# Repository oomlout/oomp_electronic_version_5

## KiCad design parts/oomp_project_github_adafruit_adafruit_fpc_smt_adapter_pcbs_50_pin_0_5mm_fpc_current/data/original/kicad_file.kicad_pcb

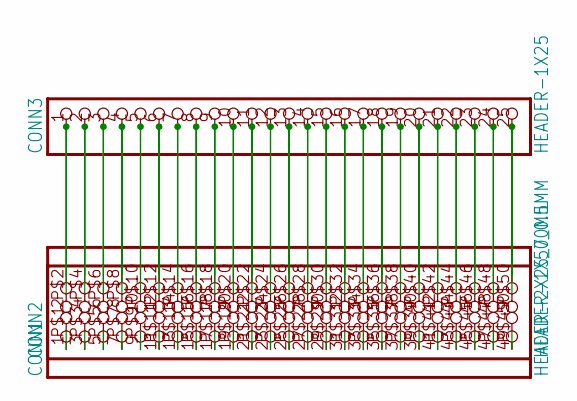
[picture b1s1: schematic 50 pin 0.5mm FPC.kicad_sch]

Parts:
CONN1: HEADER-2X25_70MIL; 2X25
CONN2: HEADER-1X50_0.5MM; FPC_GENERIC_0.5MM_50PIN
CONN3: HEADER-1X25; 1X25_ROUND_70MIL

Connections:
unnamed: CONN1.1, CONN2.P$1 (1)
unnamed: CONN1.2, CONN2.P$2 (2), CONN3.1
unnamed: CONN1.3, CONN2.P$3 (3)
unnamed: CONN1.4, CONN2.P$4 (4), CONN3.2
unnamed: CONN1.5, CONN2.P$5 (5)
unnamed: CONN1.6, CONN2.P$6 (6), CONN3.3
unnamed: CONN1.7, CONN2.P$7 (7)
unnamed: CONN1.8, CONN2.P$8 (8), CONN3.4
unnamed: CONN1.9, CONN2.P$9 (9)
unnamed: CONN1.10, CONN2.P$10 (10), CONN3.5
unnamed: CONN1.11, CONN2.P$11 (11)
unnamed: CONN1.12, CONN2.P$12 (12), CONN3.6
unnamed: CONN1.13, CONN2.P$13 (13)
unnamed: CONN1.14, CONN2.P$14 (14), CONN3.7
unnamed: CONN1.15, CONN2.P$15 (15)
unnamed: CONN1.16, CONN2.P$16 (16), CONN3.8
unnamed: CONN1.17, CONN2.P$17 (17)
unnamed: CONN1.18, CONN2.P$18 (18), CONN3.9
unnamed: CONN1.19, CONN2.P$19 (19)
unnamed: CONN1.20, CONN2.P$20 (20), CONN3.10
unnamed: CONN1.21, CONN2.P$21 (21)
unnamed: CONN1.22, CONN2.P$22 (22), CONN3.11
unnamed: CONN1.23, CONN2.P$23 (23)
unnamed: CONN1.24, CONN2.P$24 (24), CONN3.12
unnamed: CONN1.25, CONN2.P$25 (25)
unnamed: CONN1.26, CONN2.P$26 (26), CONN3.13
unnamed: CONN1.27, CONN2.P$27 (27)
unnamed: CONN1.28, CONN2.P$28 (28), CONN3.14
unnamed: CONN1.29, CONN2.P$29 (29)
unnamed: CONN1.30, CONN2.P$30 (30), CONN3.15
unnamed: CONN1.31, CONN2.P$31 (31)
unnamed: CONN1.32, CONN2.P$32 (32), CONN3.16
unnamed: CONN1.33, CONN2.P$33 (33)
unnamed: CONN1.34, CONN2.P$34 (34), CONN3.17
unnamed: CONN1.35, CONN2.P$35 (35)
unnamed: CONN1.36, CONN2.P$36 (36), CONN3.18
unnamed: CONN1.37, CONN2.P$37 (37)
unnamed: CONN1.38, CONN2.P$38 (38), CONN3.19
unnamed: CONN1.39, CONN2.P$39 (39)
unnamed: CONN1.40, CONN2.P$40 (40), CONN3.20
unnamed: CONN1.41, CONN2.P$41 (41)
unnamed: CONN1.42, CONN2.P$42 (42), CONN3.21
unnamed: CONN1.43, CONN2.P$43 (43)
unnamed: CONN1.44, CONN2.P$44 (44), CONN3.22
unnamed: CONN1.45, CONN2.P$45 (45)
unnamed: CONN1.46, CONN2.P$46 (46), CONN3.23
unnamed: CONN1.47, CONN2.P$47 (47)
unnamed: CONN1.48, CONN2.P$48 (48), CONN3.24
unnamed: CONN1.49, CONN2.P$49 (49)
unnamed: CONN1.50, CONN2.P$50 (50), CONN3.25

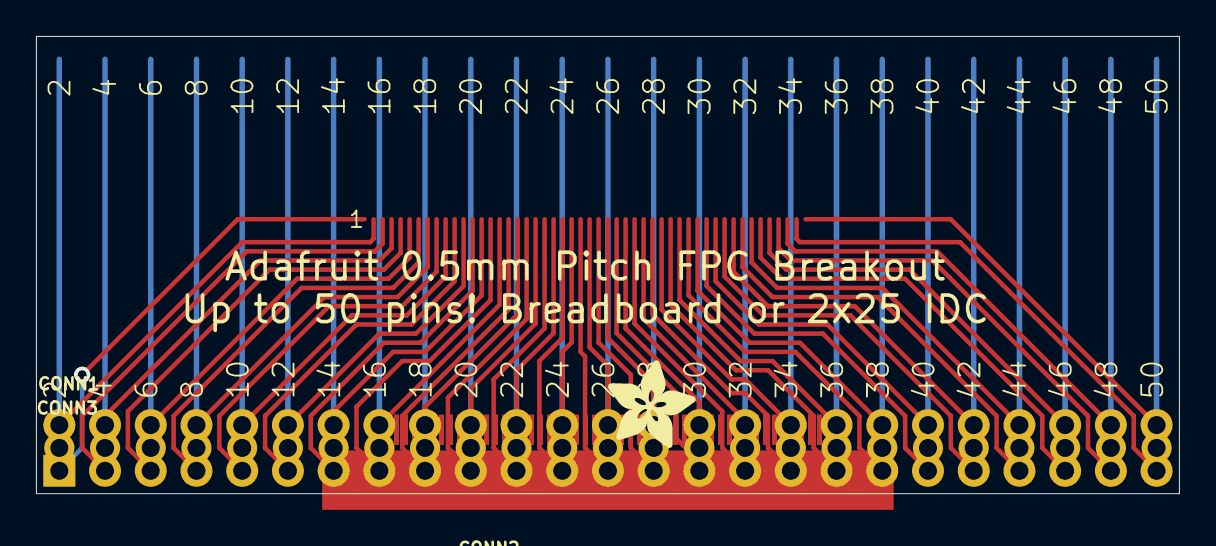
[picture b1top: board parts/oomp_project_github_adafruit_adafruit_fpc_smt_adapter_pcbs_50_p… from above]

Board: 2 copper layers, 63.5 x 25.4 mm, 4 parts (0 on the bottom side), 50 nets.

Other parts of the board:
U$1: ADAFRUIT_5MM

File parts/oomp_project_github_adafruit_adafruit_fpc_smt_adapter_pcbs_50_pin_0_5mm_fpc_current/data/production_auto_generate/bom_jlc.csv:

Comment,Designator,Footprint,LCSC Part #
,U$1,50 pin 0.5mm FPC-import-fps:ADAFRUIT_5MM,
HEADER-1X25,CONN3,50 pin 0.5mm FPC-import-fps:1X25_ROUND_70MIL,C2883713
HEADER-1X50_0.5MM,CONN2,50 pin 0.5mm FPC-import-fps:FPC_GENERIC_0.5MM_50PIN,
HEADER-2X25_70MIL,CONN1,50 pin 0.5mm FPC-import-fps:2X25,

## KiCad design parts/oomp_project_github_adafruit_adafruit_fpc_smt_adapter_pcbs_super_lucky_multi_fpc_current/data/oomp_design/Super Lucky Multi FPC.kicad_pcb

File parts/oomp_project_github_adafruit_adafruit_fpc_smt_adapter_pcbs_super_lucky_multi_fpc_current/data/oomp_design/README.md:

# OOMP KiCad design copy

Open `Super Lucky Multi FPC.kicad_pro` (or the `.kicad_pcb` / `.kicad_sch`) in KiCad. Local OOMP libraries are under `libraries/`. Original inputs are preserved in [../original/](../original/).

Only verified unchanged installed KiCad defaults were renamed. Modified, custom, unmatched and unavailable items remain unchanged. Soldering variants are never swapped during conversion. Existing pad coordinates, nets and UUIDs are preserved.

See [conversion_report.yaml](conversion_report.yaml) for every conversion and skip. Copy this directory before editing; regeneration refuses to overwrite edited design files.

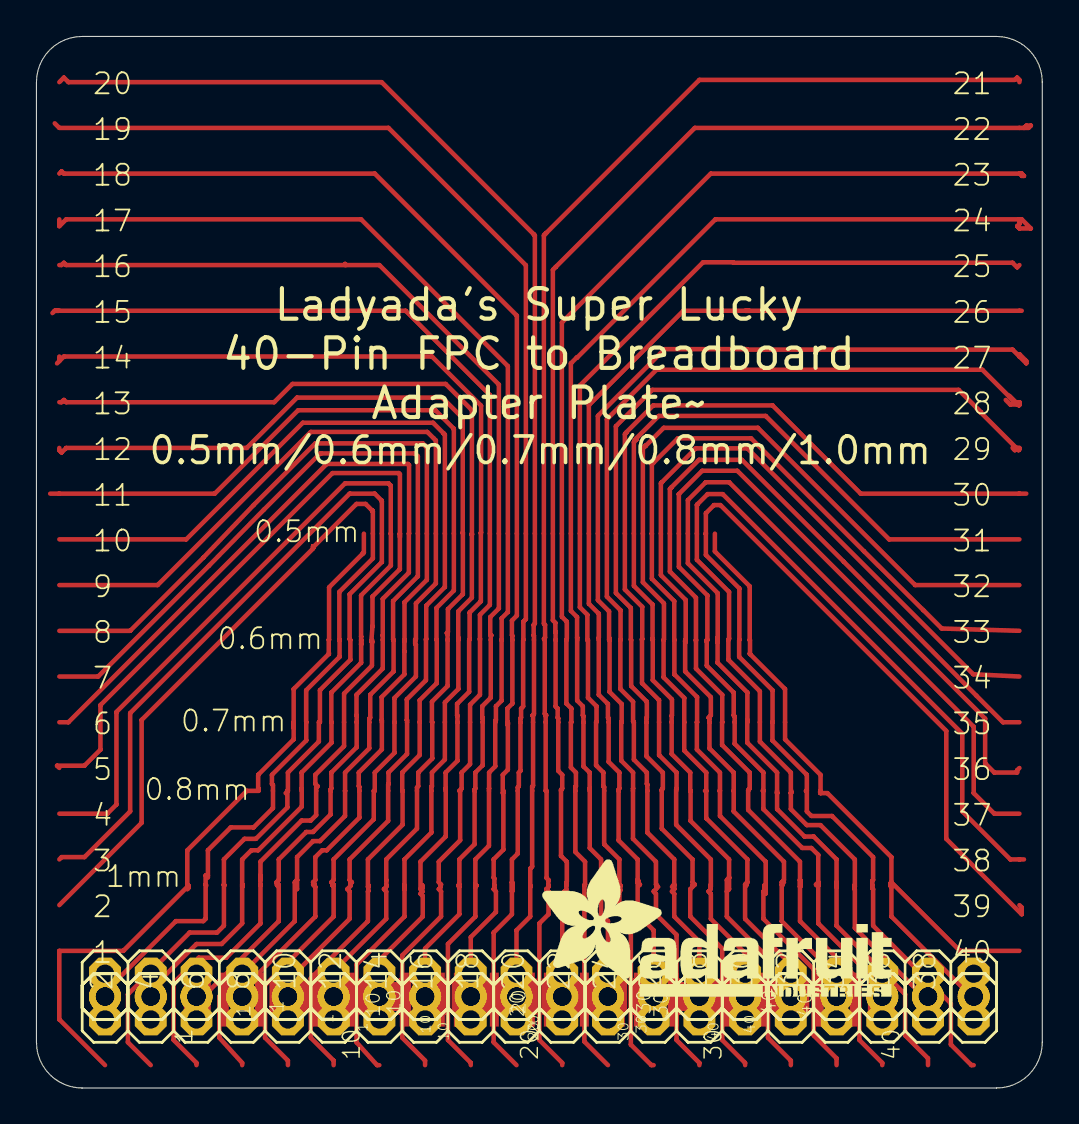
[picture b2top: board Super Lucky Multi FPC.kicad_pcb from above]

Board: 16 copper layers, 55.9 x 58.4 mm, 9 parts (0 on the bottom side), 40 nets.

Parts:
CON1: PINHD-1X40-0.5MM; 1X40-0.5MM
JP1: 2X20-BIG
JP2, JP3: 1X20-BIG
U$1: PINHD-1X40-0.6MM; 1X40-0.6MM
U$2: PINHD-1X40-0.7MM; 1X40-0.7MM
U$3: PINHD-1X40-0.8MM; 1X40-0.8MM
U$4: PINHD-1X40-1MM; 1X40-1MM
U$5: ADAFRUIT_TEXT_20MM

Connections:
unnamed: CON1.1, JP1.1, JP2.1, U$1.1, U$2.1, U$3.1, U$4.1
unnamed: CON1.2, JP1.2, JP2.2, U$1.2, U$2.2, U$3.2, U$4.2
unnamed: CON1.3, JP1.3, JP2.3, U$1.3, U$2.3, U$3.3, U$4.3
unnamed: CON1.4, JP1.4, JP2.4, U$1.4, U$2.4, U$3.4, U$4.4
unnamed: CON1.5, JP1.5, JP2.5, U$1.5, U$2.5, U$3.5, U$4.5
unnamed: CON1.6, JP1.6, JP2.6, U$1.6, U$2.6, U$3.6, U$4.6
unnamed: CON1.7, JP1.7, JP2.7, U$1.7, U$2.7, U$3.7, U$4.7
unnamed: CON1.8, JP1.8, JP2.8, U$1.8, U$2.8, U$3.8, U$4.8
unnamed: CON1.9, JP1.9, JP2.9, U$1.9, U$2.9, U$3.9, U$4.9
unnamed: CON1.10, JP1.10, JP2.10, U$1.10, U$2.10, U$3.10, U$4.10
unnamed: CON1.11, JP1.11, JP2.11, U$1.11, U$2.11, U$3.11, U$4.11
unnamed: CON1.12, JP1.12, JP2.12, U$1.12, U$2.12, U$3.12, U$4.12
unnamed: CON1.13, JP1.13, JP2.13, U$1.13, U$2.13, U$3.13, U$4.13
unnamed: CON1.14, JP1.14, JP2.14, U$1.14, U$2.14, U$3.14, U$4.14
unnamed: CON1.15, JP1.15, JP2.15, U$1.15, U$2.15, U$3.15, U$4.15
unnamed: CON1.16, JP1.16, JP2.16, U$1.16, U$2.16, U$3.16, U$4.16
unnamed: CON1.17, JP1.17, JP2.17, U$1.17, U$2.17, U$3.17, U$4.17
unnamed: CON1.18, JP1.18, JP2.18, U$1.18, U$2.18, U$3.18, U$4.18
unnamed: CON1.19, JP1.19, JP2.19, U$1.19, U$2.19, U$3.19, U$4.19
unnamed: CON1.20, JP1.20, JP2.20, U$1.20, U$2.20, U$3.20, U$4.20
unnamed: CON1.21, JP1.21, JP3.1, U$1.21, U$2.21, U$3.21, U$4.21
unnamed: CON1.22, JP1.22, JP3.2, U$1.22, U$2.22, U$3.22, U$4.22
unnamed: CON1.23, JP1.23, JP3.3, U$1.23, U$2.23, U$3.23, U$4.23
unnamed: CON1.24, JP1.24, JP3.4, U$1.24, U$2.24, U$3.24, U$4.24
unnamed: CON1.25, JP1.25, JP3.5, U$1.25, U$2.25, U$3.25, U$4.25
unnamed: CON1.26, JP1.26, JP3.6, U$1.26, U$2.26, U$3.26, U$4.26
unnamed: CON1.27, JP1.27, JP3.7, U$1.27, U$2.27, U$3.27, U$4.27
unnamed: CON1.28, JP1.28, JP3.8, U$1.28, U$2.28, U$3.28, U$4.28
unnamed: CON1.29, JP1.29, JP3.9, U$1.29, U$2.29, U$3.29, U$4.29
unnamed: CON1.30, JP1.30, JP3.10, U$1.30, U$2.30, U$3.30, U$4.30
unnamed: CON1.31, JP1.31, JP3.11, U$1.31, U$2.31, U$3.31, U$4.31
unnamed: CON1.32, JP1.32, JP3.12, U$1.32, U$2.32, U$3.32, U$4.32
unnamed: CON1.33, JP1.33, JP3.13, U$1.33, U$2.33, U$3.33, U$4.33
unnamed: CON1.34, JP1.34, JP3.14, U$1.34, U$2.34, U$3.34, U$4.34
unnamed: CON1.35, JP1.35, JP3.15, U$1.35, U$2.35, U$3.35, U$4.35
unnamed: CON1.36, JP1.36, JP3.16, U$1.36, U$2.36, U$3.36, U$4.36
unnamed: CON1.37, JP1.37, JP3.17, U$1.37, U$2.37, U$3.37, U$4.37
unnamed: CON1.38, JP1.38, JP3.18, U$1.38, U$2.38, U$3.38, U$4.38
unnamed: CON1.39, JP1.39, JP3.19, U$1.39, U$2.39, U$3.39, U$4.39
unnamed: CON1.40, JP1.40, JP3.20, U$1.40, U$2.40, U$3.40, U$4.40

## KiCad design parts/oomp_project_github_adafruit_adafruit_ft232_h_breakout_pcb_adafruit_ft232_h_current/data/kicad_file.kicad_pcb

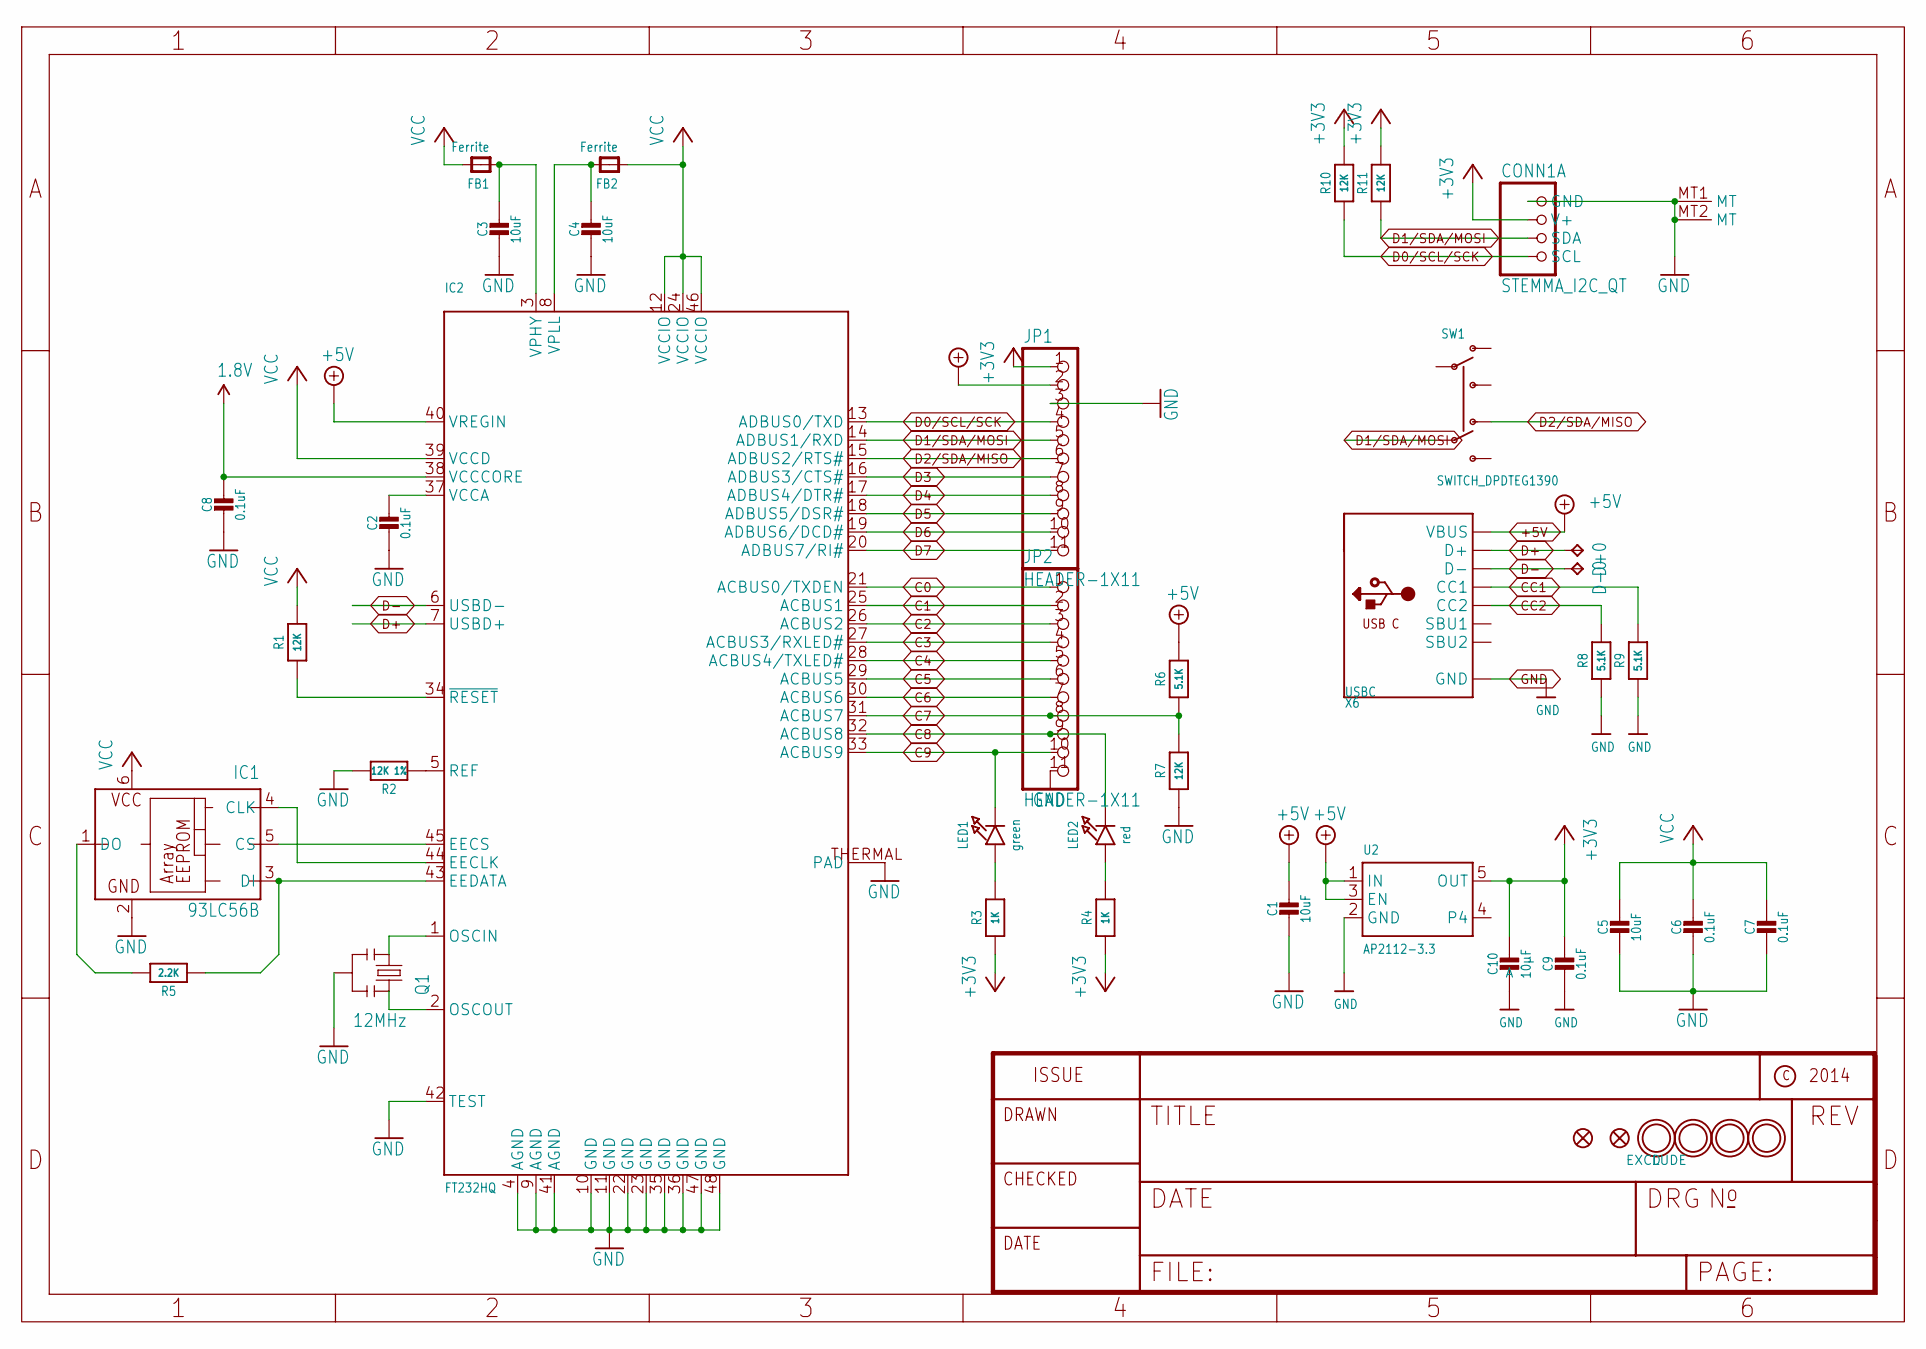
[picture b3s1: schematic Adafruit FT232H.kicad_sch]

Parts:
C1, C3, C4, C5: 10uF; 0805-NO
C2, C6, C7, C8, C9: 0.1uF; 0603-NO
C10: 10µF; 0805-NO
CONN1: STEMMA_I2C_QT; JST_SH4
D+0: TPTP17R; TP17R
D-0: TPTP17R; TP17R
FB1, FB2: Ferrite; _0805
FID1, FID2: FIDUCIAL""; FIDUCIAL_1MM
IC1: 93LC56B; SOT23-6; MPN 93LC76AT-I/OT
IC2: FT232HQ; QFN48_8MM
JP1, JP2: HEADER-1X11; 1X11_ROUND
LED1: green; CHIPLED_0805_NOOUTLINE
LED2: red; CHIPLED_0805_NOOUTLINE
Q1: 12MHz; RESONATOR-SMD
R1, R7, R10, R11: 12K; 0603-NO
R2: 12K 1%; 0603-NO
R3, R4: 1K; 0603-NO
R5: 2.2K; 0603-NO
R6, R8, R9: 5.1K; 0603-NO
SW1: SWITCH_DPDTEG1390; EG1390
U2: AP2112-3.3; SOT23-5
U$4, U$5, U$6, U$7: MOUNTINGHOLE2.5; MOUNTINGHOLE_2.5_PLATED
X6: USBC; USB_C_CUSB31-CFM2AX-01-X

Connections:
1.8V: C8.1, IC2.38 (VCCCORE)
+3V3: C9.1, C10.1, CONN1.2 (V+), JP1.1, R3.1, R4.1, R10.2, R11.2, U2.5 (OUT)
+5V: C1.1, IC2.40 (VREGIN), JP1.2, R6.2, U2.1 (IN), U2.3 (EN), X6.A4B9 (VBUS), X6.B4A9 (VBUS)
C0: IC2.21 (ACBUS0/TXDEN), JP2.1
C1: IC2.25 (ACBUS1), JP2.2
C2: IC2.26 (ACBUS2), JP2.3
C3: IC2.27 (ACBUS3/RXLED#), JP2.4
C4: IC2.28 (ACBUS4/TXLED#), JP2.5
C5: IC2.29 (ACBUS5), JP2.6
C6: IC2.30 (ACBUS6), JP2.7
C7: IC2.31 (ACBUS7), JP2.8, R6.1, R7.2
C8: IC2.32 (ACBUS8), JP2.9, LED2.C
C9: IC2.33 (ACBUS9), JP2.10, LED1.C
CC1: R9.2, X6.A5 (CC1)
CC2: R8.2, X6.B5 (CC2)
D0/SCL/SCK: CONN1.4 (SCL), IC2.13 (ADBUS0/TXD), JP1.4, R10.1
D1/SDA/MOSI: CONN1.3 (SDA), IC2.14 (ADBUS1/RXD), JP1.5, R11.1, SW1.P2
D2/SDA/MISO: IC2.15 (ADBUS2/RTS#), JP1.6, SW1.O2
D3: IC2.16 (ADBUS3/CTS#), JP1.7
D4: IC2.17 (ADBUS4/DTR#), JP1.8
D5: IC2.18 (ADBUS5/DSR#), JP1.9
D6: IC2.19 (ADBUS6/DCD#), JP1.10
D7: IC2.20 (ADBUS7/RI#), JP1.11
D+: D+0.TP, IC2.7 (USBD+), X6.A6 (D+), X6.B6 (D+)
D-: D-0.TP, IC2.6 (USBD-), X6.A7 (D-), X6.B7 (D-)
GND: C1.2, C2.2, C3.2, C4.2, C5.2, C6.2, C7.2, C8.2, C9.2, C10.2, CONN1.1 (GND), CONN1.MT1 (MT), CONN1.MT2 (MT), IC1.2 (GND), IC2.4 (AGND), IC2.9 (AGND), IC2.10 (GND), IC2.11 (GND), IC2.22 (GND), IC2.23 (GND), IC2.35 (GND), IC2.36 (GND), IC2.41 (AGND), IC2.42 (TEST), IC2.47 (GND), IC2.48 (GND), IC2.THERMAL (PAD), JP1.3, JP2.11, Q1.2, R2.2, R7.1, R8.1, R9.1, U2.2 (GND), X6.A1B12 (GND), X6.B1A12 (GND)
unnamed: IC2.1 (OSCIN), Q1.1
unnamed: IC2.2 (OSCOUT), Q1.3
unnamed: IC2.5 (REF), R2.1
unnamed: LED2.A, R4.2
unnamed: IC2.34 (~RESET), R1.1
unnamed: LED1.A, R3.2
unnamed: IC1.3 (DI), IC2.43 (EEDATA), R5.1
unnamed: IC1.5 (CS), IC2.45 (EECS)
unnamed: IC1.4 (CLK), IC2.44 (EECLK)
unnamed: IC1.1 (DO), R5.2
VCC: C5.1, C6.1, C7.1, FB1.2, FB2.1, IC1.6 (VCC), IC2.12 (VCCIO), IC2.24 (VCCIO), IC2.39 (VCCD), IC2.46 (VCCIO), R1.2
VCCA: C2.1, IC2.37 (VCCA)
VPHY: C3.1, FB1.1, IC2.3 (VPHY)
VPLL: C4.1, FB2.2, IC2.8 (VPLL)

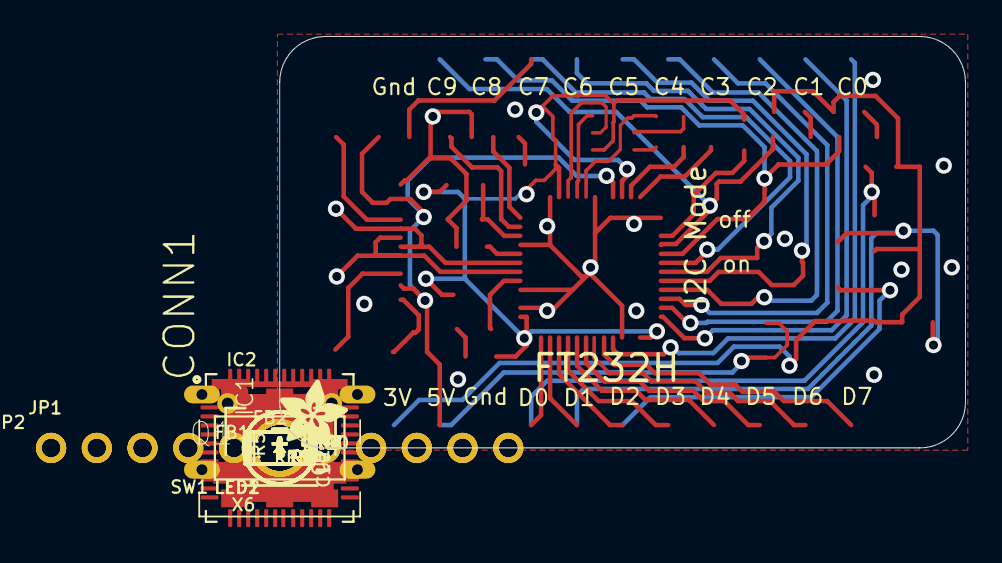
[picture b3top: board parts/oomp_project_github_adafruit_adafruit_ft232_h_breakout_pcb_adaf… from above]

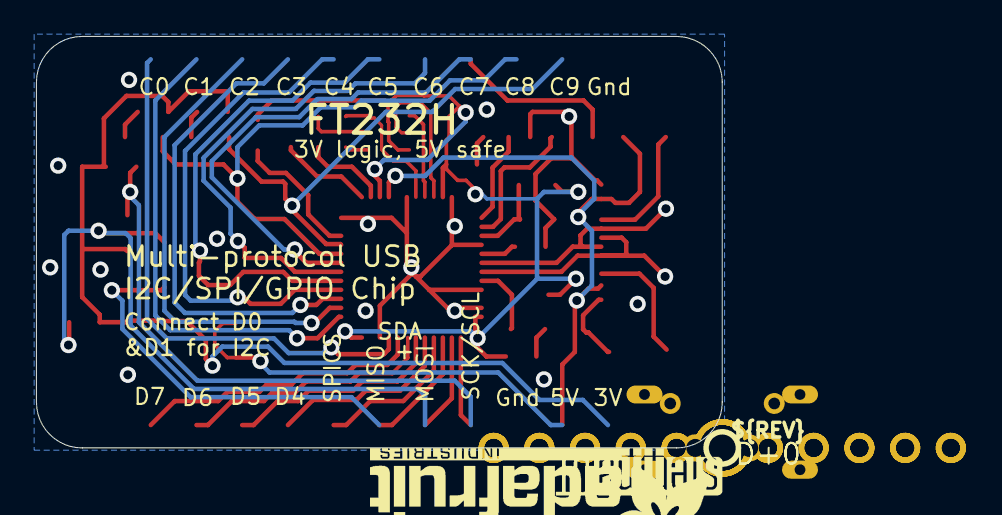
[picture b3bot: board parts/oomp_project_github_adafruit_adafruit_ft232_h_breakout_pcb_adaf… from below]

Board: 2 copper layers, 38.1 x 22.9 mm, 46 parts (5 on the bottom side), 40 nets.

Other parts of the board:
U$2: ADAFRUIT_3.5MM
U$3: ADAFRUIT_TEXT_20MM
U$8: STEMMAQT
U$11: PCBFEAT-REV-040

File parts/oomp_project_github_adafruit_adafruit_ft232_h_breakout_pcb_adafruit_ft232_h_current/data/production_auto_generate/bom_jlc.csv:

Comment,Designator,Footprint,LCSC Part #
,"JP1,JP2",Adafruit FT232H-import-fps:1X11_ROUND,C2894934
,U$2,Adafruit FT232H-import-fps:ADAFRUIT_3.5MM,
,U$3,Adafruit FT232H-import-fps:ADAFRUIT_TEXT_20MM,
,SW1,Adafruit FT232H-import-fps:EG1390,
,U$11,Adafruit FT232H-import-fps:PCBFEAT-REV-040,
,U$8,Adafruit FT232H-import-fps:STEMMAQT,
0.1uF,"C2,C6,C7,C8,C9",Adafruit FT232H-import-fps:0603-NO,C14663
10uF,"C1,C3,C4,C5",Adafruit FT232H-import-fps:0805-NO,
10µF,C10,Adafruit FT232H-import-fps:0805-NO,
12K,"R1,R7,R10,R11",Adafruit FT232H-import-fps:0603-NO,C2906989
12K 1%,R2,Adafruit FT232H-import-fps:0603-NO,C2906989
12MHz,Q1,Adafruit FT232H-import-fps:RESONATOR-SMD,
1K,"R3,R4",Adafruit FT232H-import-fps:0603-NO,C2907002
2.2K,R5,Adafruit FT232H-import-fps:0603-NO,C4190
5.1K,"R6,R8,R9",Adafruit FT232H-import-fps:0603-NO,C23186
93LC56B,IC1,Adafruit FT232H-import-fps:SOT23-6,
AP2112-3.3,U2,Adafruit FT232H-import-fps:SOT23-5,
Ferrite,"FB1,FB2",Adafruit FT232H-import-fps:_0805,
FT232HQ,IC2,Adafruit FT232H-import-fps:QFN48_8MM,
green,LED1,Adafruit FT232H-import-fps:CHIPLED_0805_NOOUTLINE,
red,LED2,Adafruit FT232H-import-fps:CHIPLED_0805_NOOUTLINE,
STEMMA_I2C_QT,CONN1,Adafruit FT232H-import-fps:JST_SH4,C160404
TPTP17R,"D+0,D-0",Adafruit FT232H-import-fps:TP17R,
USBC,X6,Adafruit FT232H-import-fps:USB_C_CUSB31-CFM2AX-01-X,
